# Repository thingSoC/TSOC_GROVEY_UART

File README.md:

# TSOC_GROVEY_UART

The thingSoC GROVEY_UART Base board incorporates a Cypress CY7C65215 Dual Channel USB Bridge, that supports UART, I2C, SPI, and JTAG interfaces in a thingSoC format.

The thingSoC GROVEY_UART Base board has two USB bridge channels, which can be programmed to be either UART, I2C, SPI, JTAG, or Capacitance Sensing (buttons/sliders) Human Input devices.

USB Bridge One (Port 1) and USB Bridge Two (Port 2) are both connected to Grove System compatible connectors, and USB Bridge One (Port 1) is also connected to the thingSoC standard UART channel.

Port1 can be used to program a target microprocessor, at the same time Port2 is used for another purpose (i.e. debug channel, USB to RS-485 bridge, etc).  

It's like having two (2) FTDI adapters in One!

[ 
TSOC_GROVEY_UART](https://github.com/thingSoC/TSOC_GROVEY_UART)

---------------------------------------
## Use it as a Programming Dongle

---------------------------------------
## Use it as a Protocol Adapter

---------------------------------------
## TSOC_GROVEY_UART Model Images

[ 
TSOC_GROVEY_UART](https://github.com/thingSoC/TSOC_GROVEY_UART)

[ 
TSOC_GROVEY_UART](https://github.com/thingSoC/TSOC_GROVEY_UART)

---------------------------------------

## TSOC_GROVEY_UART Status <a name="TSOC_GROVEY_UART_status"/>

Revision 1.0 - 09/02/2016

---------------------------------------

## TSOC_GROVEY_UART Documentation Index <a name="TSOC_GROVEY_UART_documentation_index"/>

[TSOC_GROVEY_UART Project](https://github.com/thingSoC/TSOC_GROVEY_UART/)

[TSOC_GROVEY_UART Hardware](https://github.com/thingSoC/TSOC_GROVEY_UART/tree/master/TSOC_GROVEY_UART/hardware)

---------------------------------------

## thingSoC Documentation Index <a name="thingSoC_documentation_index"/>

[thingSoC Organization Website](http://thingSoC.github.io)

[thingSoC FAQ - Frequently Asked Questions](http://thingsoc.github.io/support/faq.html)

---------------------------------------

[ 
*thingSoC*](http://thingsoc.github.io)

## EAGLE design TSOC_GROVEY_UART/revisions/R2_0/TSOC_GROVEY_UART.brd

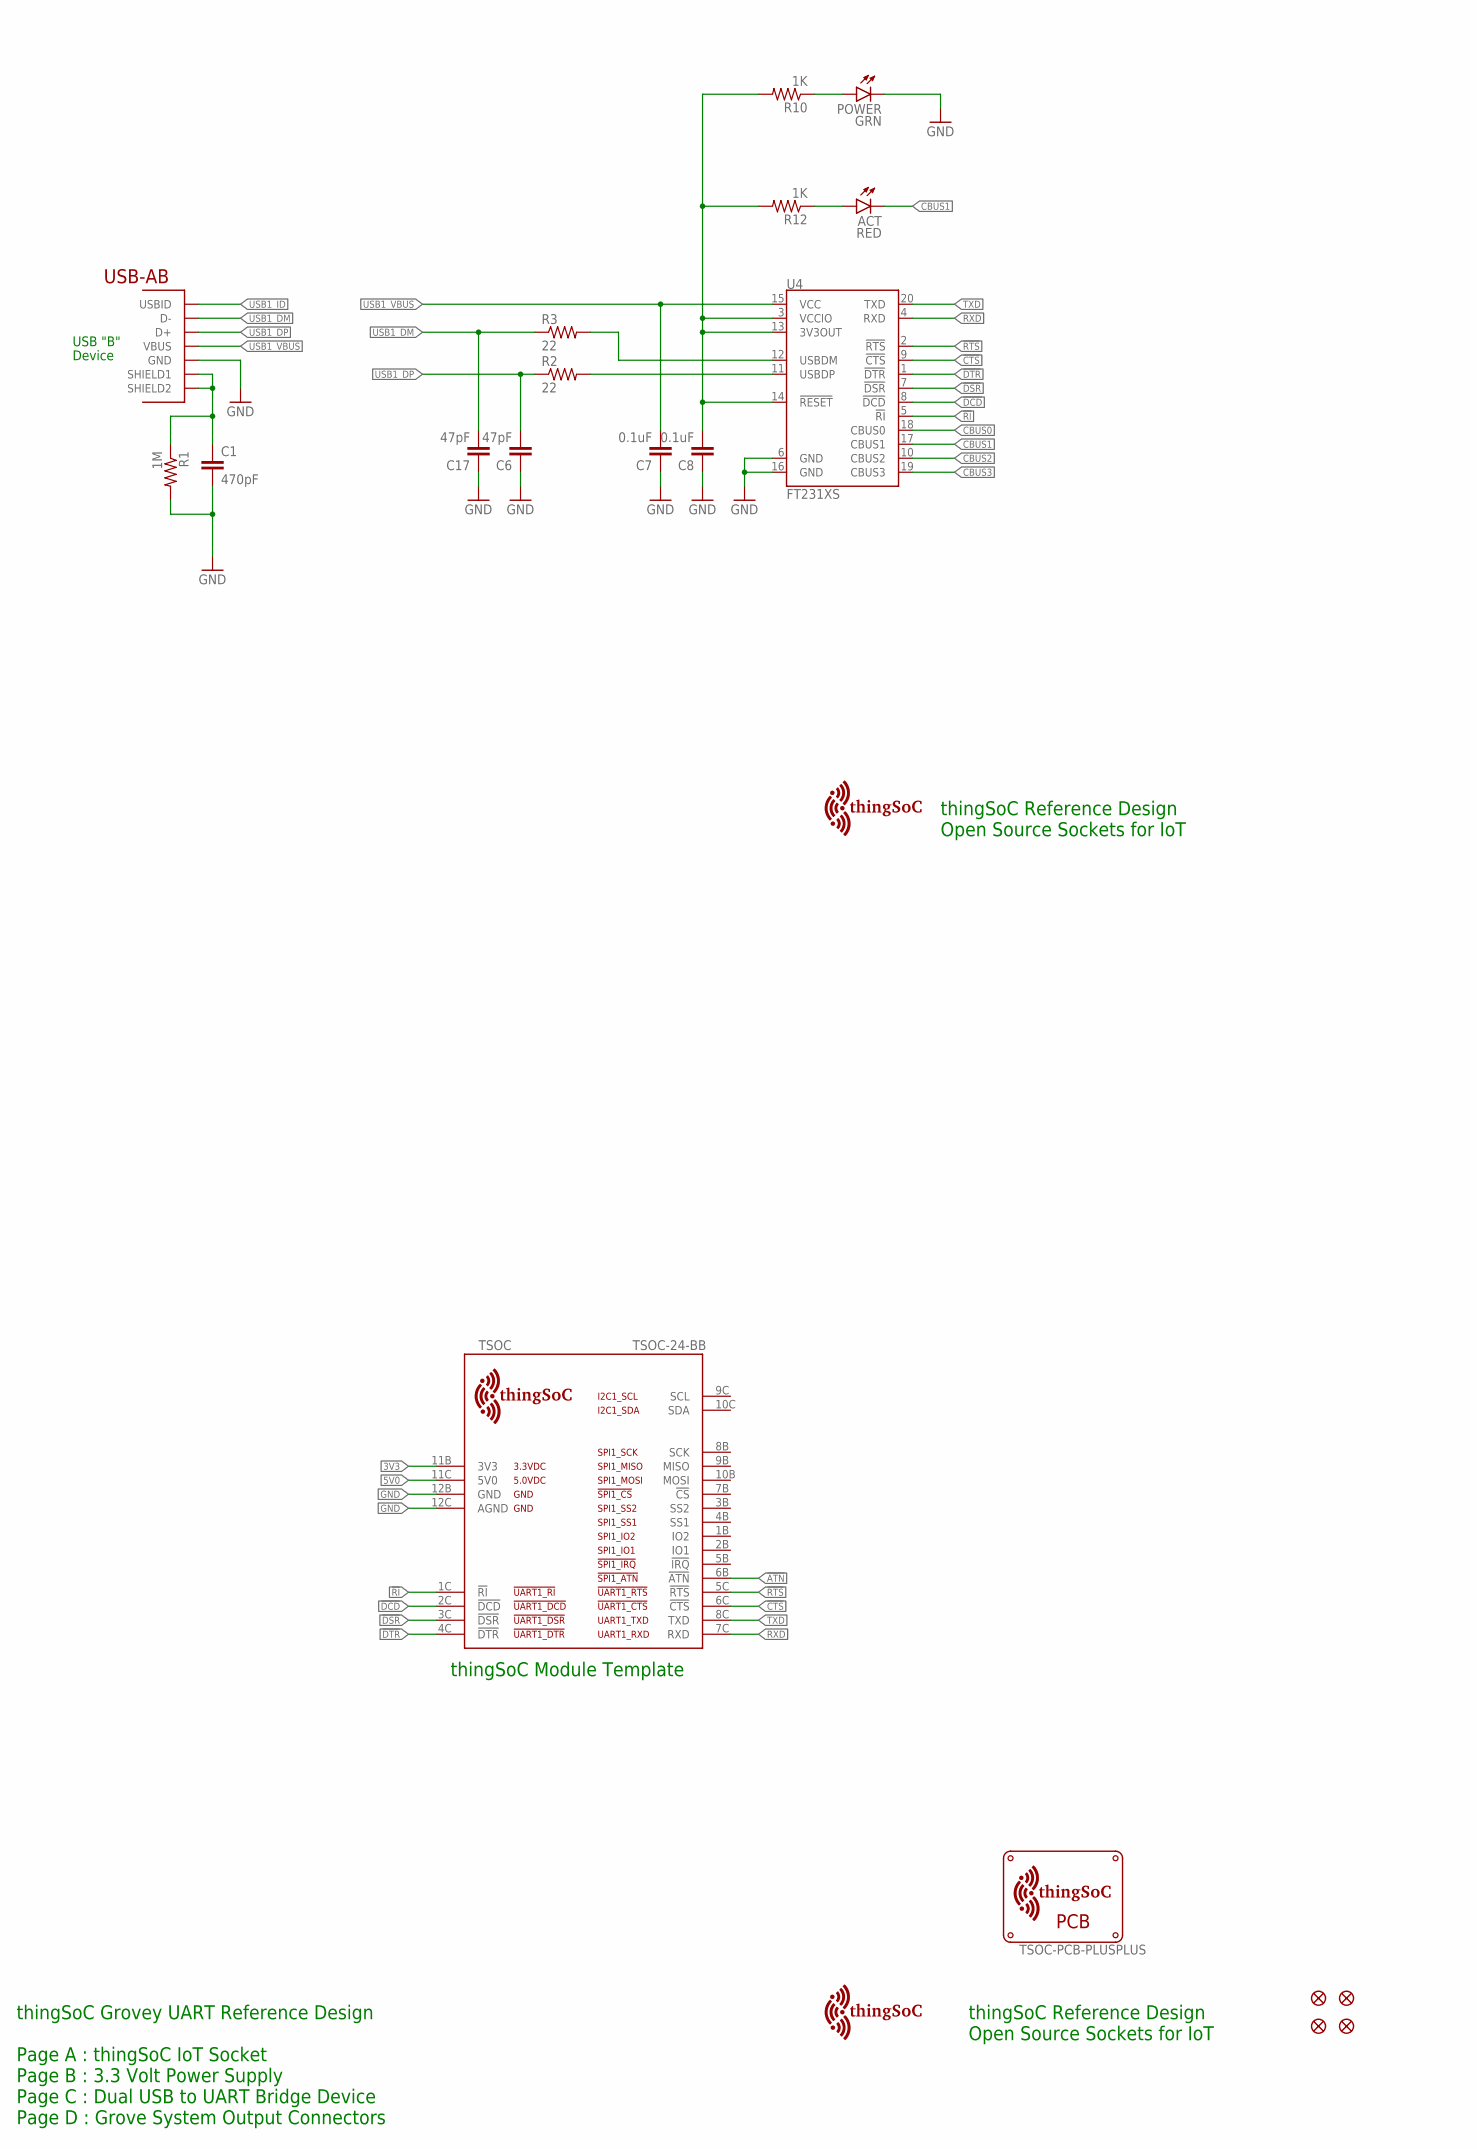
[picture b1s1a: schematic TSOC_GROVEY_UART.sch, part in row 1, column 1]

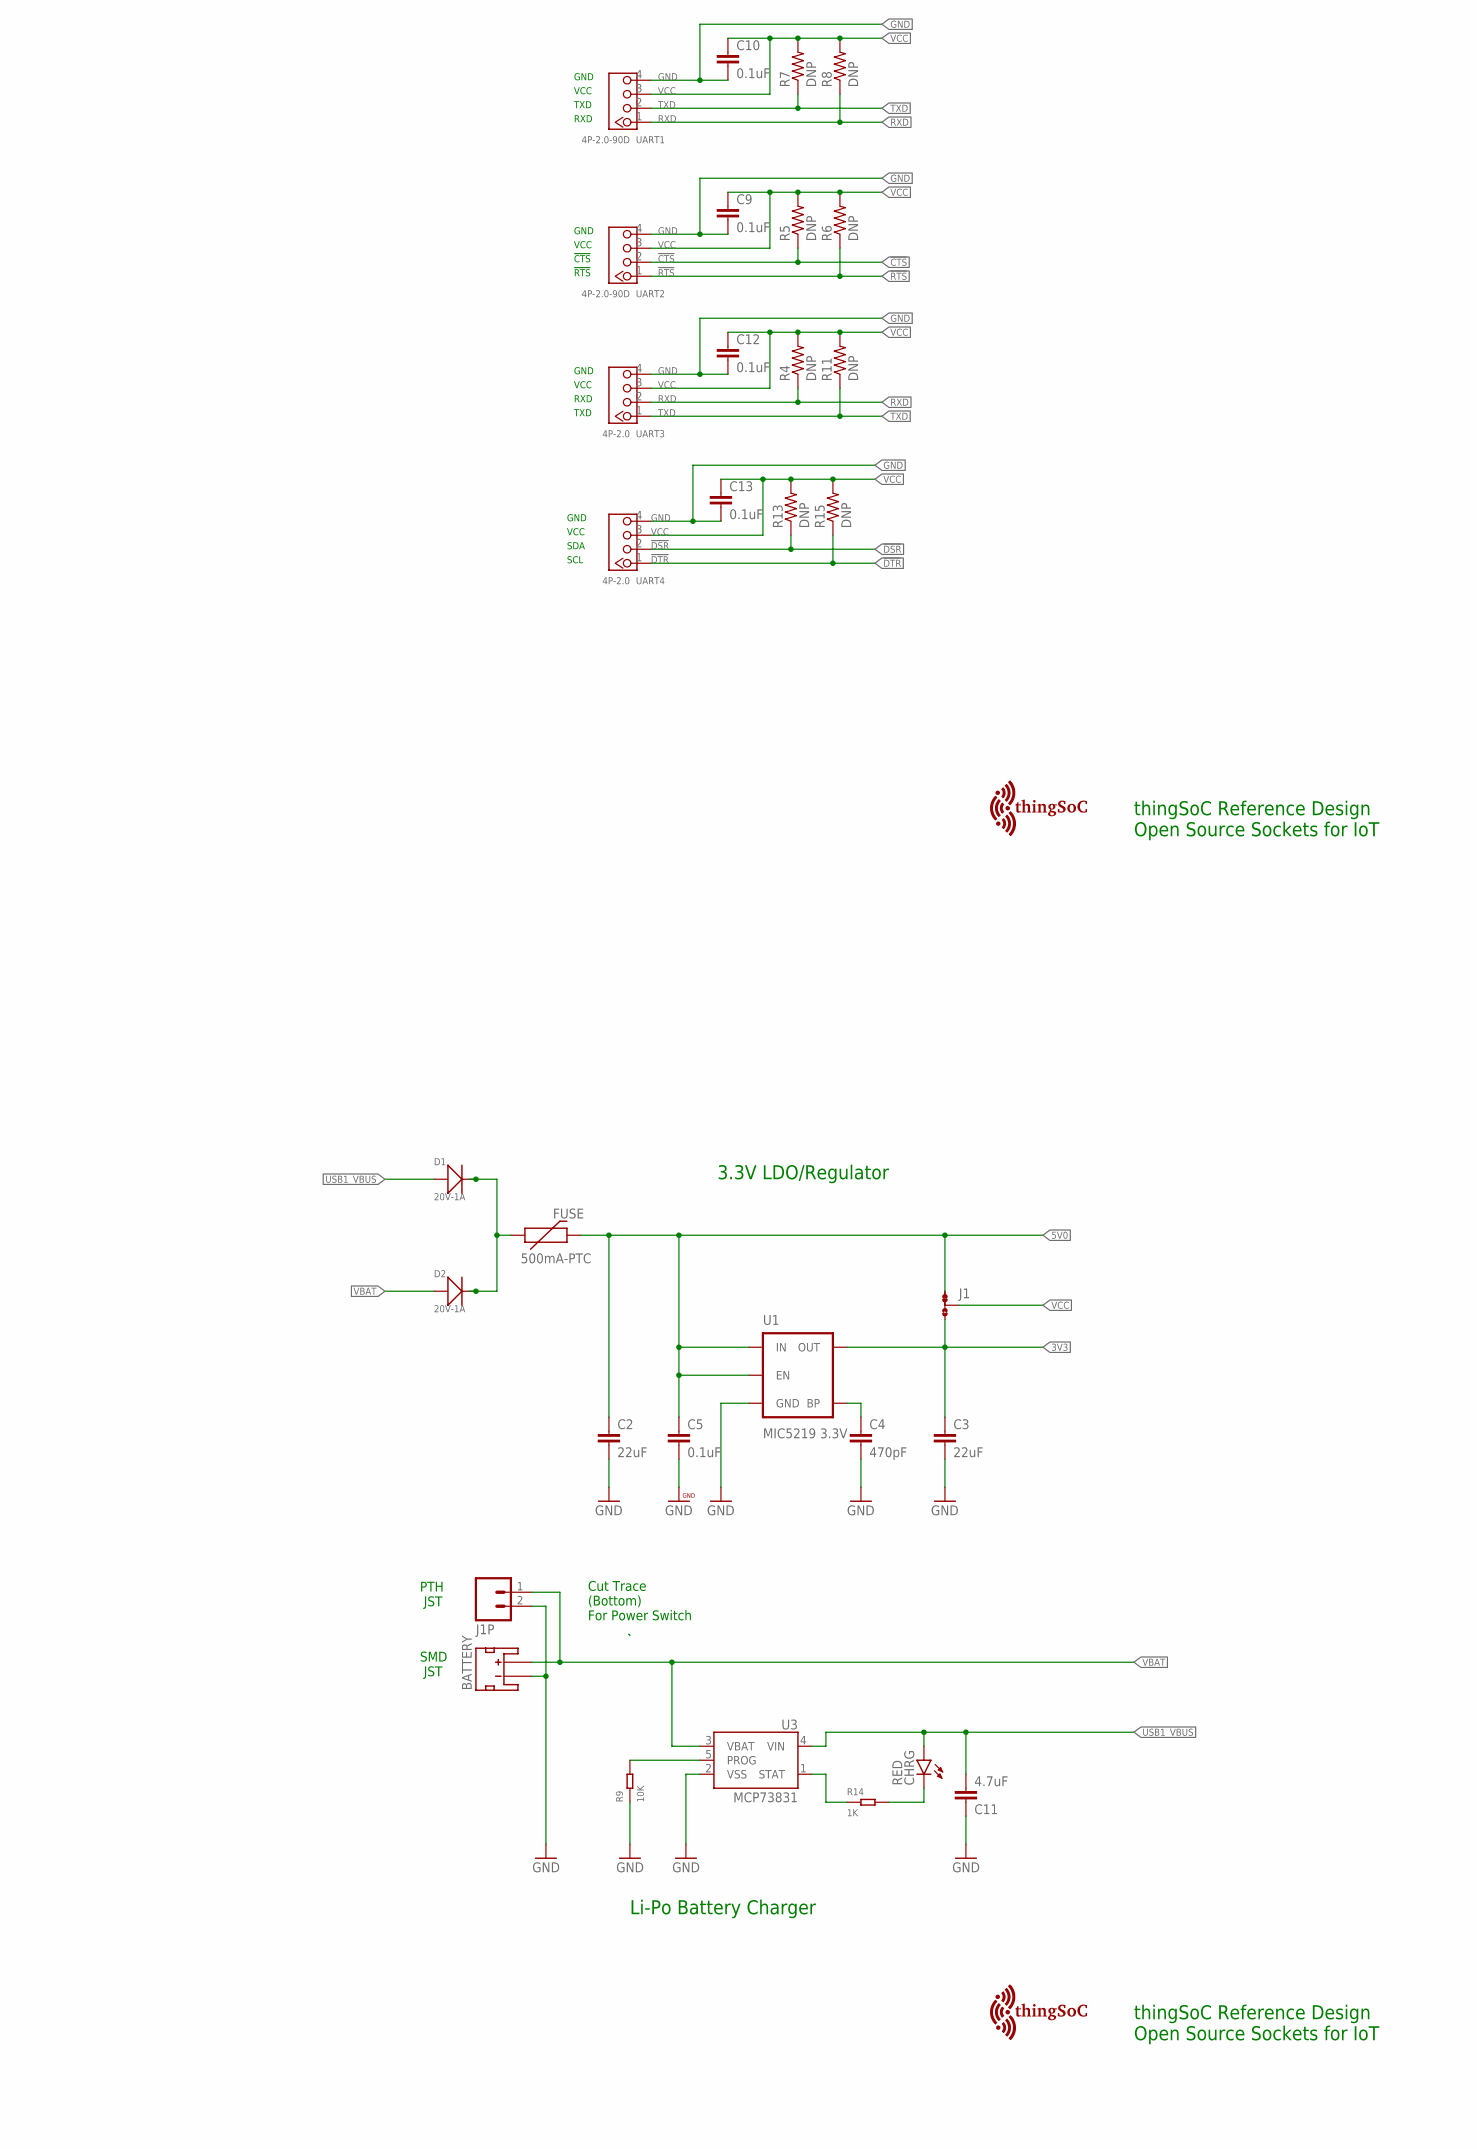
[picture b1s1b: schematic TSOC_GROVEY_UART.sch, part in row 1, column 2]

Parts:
ACT: RED; LED-0603
BATTERY: JST_2MM_MALE; JST-2-SMD
C1, C4: 470pF; EIA-0603
C2, C3: 22uF; EIA-1206
C5, C7, C8: 0.1uF; EIA-0603
C6, C17: 47pF; EIA-0603
C9, C10, C12, C13: 0.1uF; 0603-CAP
C11: 4.7uF; 0402-CAP
CHRG: RED; LED-0603
D1, D2: 20V-1A; SOD-123
FID1, FID2, FID3, FID4: FIDUCIALUFIDUCIAL; MICRO-FIDUCIAL
FUSE: 500mA-PTC; PTC-1206
J1: JMP-3-1_2
J1P: M02-JST-2-PTH-NO_SILK; JST-2-PTH-NS
POWER: GRN; LED-0603
R1: 1M; EIA-0603
R2, R3: 22; EIA-0603
R4, R5, R6, R7, R8, R11, R13, R15: DNP; 0603-RES
R9: 10K; R0603
R10, R12: 1K; EIA-0603
R14: 1K; R0603
TSOC: TSOC-24-BB; TSOC-BB-S24
U1: MIC5219 3.3V; SOT23-5
U3: MCP73831; SOT23-5
U4: FT231XS; SSOP20_L
U$3: TSOC-LOGO-LRG
U$4, U$5, U$6: TSOC-LOGO; TSOC-LOGO-BLANK
U$8: TSOC-PCB-PLUSPLUS; TSOC-BB-BRD-PLUS-PLUS-DIM
UART1, UART2: 4P-2.0-90D; HW4-2.0-90D
UART3, UART4: 4P-2.0; HW4-2.0
USB: USB_AB; USB-AB-MICRO-SMD

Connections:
3V3: C3.1, J1.3, TSOC.11B (3V3), U1.5 (OUT)
3V3U: C8.2, R10.2, R12.2, U4.3 (VCCIO), U4.13 (3V3OUT), U4.14 (!RESET)
5V0: C2.1, C5.1, FUSE.2, J1.1, TSOC.11C (5V0), U1.1 (IN), U1.3 (EN)
!ATN: TSOC.6B (!ATN)
!CTS: R5.1, TSOC.6C (!CTS), U4.9 (!CTS), UART2.2
!DCD: TSOC.2C (!DCD), U4.8 (!DCD)
!DSR: R13.1, TSOC.3C (!DSR), U4.7 (!DSR), UART4.2
!DTR: R15.1, TSOC.4C (!DTR), U4.1 (!DTR), UART4.1
!RI: TSOC.1C (!RI), U4.5 (!RI)
!RTS: R6.1, TSOC.5C (!RTS), U4.2 (!RTS), UART2.1
BYPASS1: C4.1, U1.4 (BP)
CBUS0: U4.18 (CBUS0)
CBUS1: ACT.C, U4.17 (CBUS1)
CBUS2: U4.10 (CBUS2)
CBUS3: U4.19 (CBUS3)
CLED: CHRG.C, R14.2
CSTAT: R14.1, U3.1 (STAT)
GND: BATTERY.1 (-), C1.2, C2.2, C3.2, C4.2, C5.2, C6.1, C7.1, C8.1, C9.2, C10.2, C11.1, C12.2, C13.2, C17.1, J1P.2, POWER.C, R1.2, R9.1, TSOC.12B (GND), TSOC.12C (AGND), U1.2 (GND), U3.2 (VSS), U4.6 (GND), U4.16 (GND), UART1.4, UART2.4, UART3.4, UART4.4, USB.GND
GRN: POWER.A, R10.1
unnamed: D1.-, D2.-, FUSE.1
RXD: R4.1, R8.1, TSOC.7C (RXD), U4.4 (RXD), UART1.1, UART3.2
TXD: R7.1, R11.1, TSOC.8C (TXD), U4.20 (TXD), UART1.2, UART3.1
USB1_DM: C17.2, R3.1, USB.D-
USB1_DP: C6.2, R2.1, USB.D+
USB1_ID: USB.ID (USBID)
USB1_M: R3.2, U4.12 (USBDM)
USB1_P: R2.2, U4.11 (USBDP)
USB1_SHIELD: C1.1, R1.1, USB.SHIELD1, USB.SHIELD2
USB1_VBUS: C7.2, C11.2, CHRG.A, D1.+, U3.4 (VIN), U4.15 (VCC), USB.VBUS
VBAT: BATTERY.2 (+), D2.+, J1P.1, U3.3 (VBAT)
VB_PROG: R9.2, U3.5 (PROG)
VCC: C9.1, C10.1, C12.1, C13.1, J1.2, R4.2, R5.2, R6.2, R7.2, R8.2, R11.2, R13.2, R15.2, UART1.3, UART2.3, UART3.3, UART4.3
YEL: ACT.A, R12.1

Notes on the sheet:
thingSoC Reference Design Open Source Sockets for IoT
USB "B"
Device
thingSoC Grovey UART Reference Design Page A : thingSoC IoT Socket Page B : 3.3 Volt Power Supply Page C : Dual USB to UART Bridge Device Page D : Grove System Output Connectors
thingSoC Module Template
3.3V LDO/Regulator
GND
VCC
RXD
TXD
!CTS
!RTS
Li-Po Battery Charger
Cut Trace (Bottom) For Power Switch
SMD JST
PTH JST
SDA
SCL

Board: 2 copper layers, 58 parts (2 on the bottom side), 28 nets, no tracks yet.

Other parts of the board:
U$1, U$7: TSOC-LOGO-SMALL; TSOC-LOGO-SML

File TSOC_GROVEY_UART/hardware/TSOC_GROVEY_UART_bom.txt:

Partlist exported from /data/customers/PatternAgents/eagle/TSOC_Modules/TSOC_GROVEY_UART/TSOC_GROVEY_UART/TSOC_GROVEY_UART.sch at 8/25/16 1:26 PM

Qty Value              Device                          Package                  Parts                  Description                                                                                                                                                                               
2                      JMP-2-NO                        JMP-2-NO                 SCL, SDA               Two Terminal Jumper - Normally Open                                                                                                                                                       
3   0.1uF              CAP-0603                        EIA-0603                 C5, C7, C8             Ceramic Capacitor SMD                                                                                                                                                                     
2   0.1uF              CAP0603-CAP                     0603-CAP                 C9, C10                Capacitor                                                                                                                                                                                 
1   1.0uF              CAP-0603                        EIA-0603                 C6                     Ceramic Capacitor SMD                                                                                                                                                                     
2   10K                RESISTOR-0603                   EIA-0603                 R15, R17                                                                                                                                                                                                         
4   1K                 RESISTOR-0603                   EIA-0603                 R4, R10, R11, R12                                                                                                                                                                                                
1   1M                 RESISTOR-0603                   EIA-0603                 R1                                                                                                                                                                                                               
2   22                 RESISTOR-0603                   EIA-0603                 R2, R3                                                                                                                                                                                                           
1   22K                RESISTOR-0603                   EIA-0603                 R13                                                                                                                                                                                                              
2   22uF               CAP-1206                        EIA-1206                 C2, C3                 Ceramic Capacitor SMD                                                                                                                                                                     
2   470pF              CAP-0603                        EIA-0603                 C1, C4                 Ceramic Capacitor SMD                                                                                                                                                                     
2   4P-2.0-90D         GROVE-CONNECTOR-DIP-90D(4P-2.0) HW4-2.0-90D              UART1, UART2           320110034                                                                                                                                                                                 
1   500mA-PTC          PTCSMD                          PTC-1206                 FUSE                   Resettable Fuse PTC                                                                                                                                                                       
1   BLUE               LED0603                         LED-0603                 PORT2                  LEDs                                                                                                                                                                                      
1   CY7C65215-32-PROTO CY7C65215-32-PROTO              QFN32-PROTO              U2                     Cypress EZ-USB ® CY7C65215-32QFN DUAL CHANNEL USB TO UART/SPI/IC Bridge                                                                                                                   
4   DNP                RESISTOR0603-RES                0603-RES                 R5, R6, R7, R8         Resistor                                                                                                                                                                                  
4   FIDUCIALUFIDUCIAL  FIDUCIALUFIDUCIAL               MICRO-FIDUCIAL           FID1, FID2, FID3, FID4 Fiducial Alignment Points                                                                                                                                                                 
1   GRN                LED0603                         LED-0603                 POWER                  LEDs                                                                                                                                                                                      
2   JMP-3-1_2          JMP-3-1_2                       JMP-3-1_2                J1, J2                 Three Terminal Jumper - 1 & 2 Connected                                                                                                                                                   
1   MIC5219 3.3V       V_REG_MIC52193.3V               SOT23-5                  U1                     V_REG MIC5219                                                                                                                                                                             
1   RED                LED0603                         LED-0603                 SUSPEND                LEDs                                                                                                                                                                                      
1   SP1001-02JTG       SP1001-02JTG                    SC70-3                   ESD                    Littelfuse SP1001-02JTG TVS Diode Array 8pf 15kV Source: 
1   USB_AB             USB_AB                          USB-AB-MICRO-SMD         USB                    This is a USB AB connector that is compatible with USB OTG.                                                                            
1   YELLOW             LED0603                         LED-0603                 PORT1                  LEDs

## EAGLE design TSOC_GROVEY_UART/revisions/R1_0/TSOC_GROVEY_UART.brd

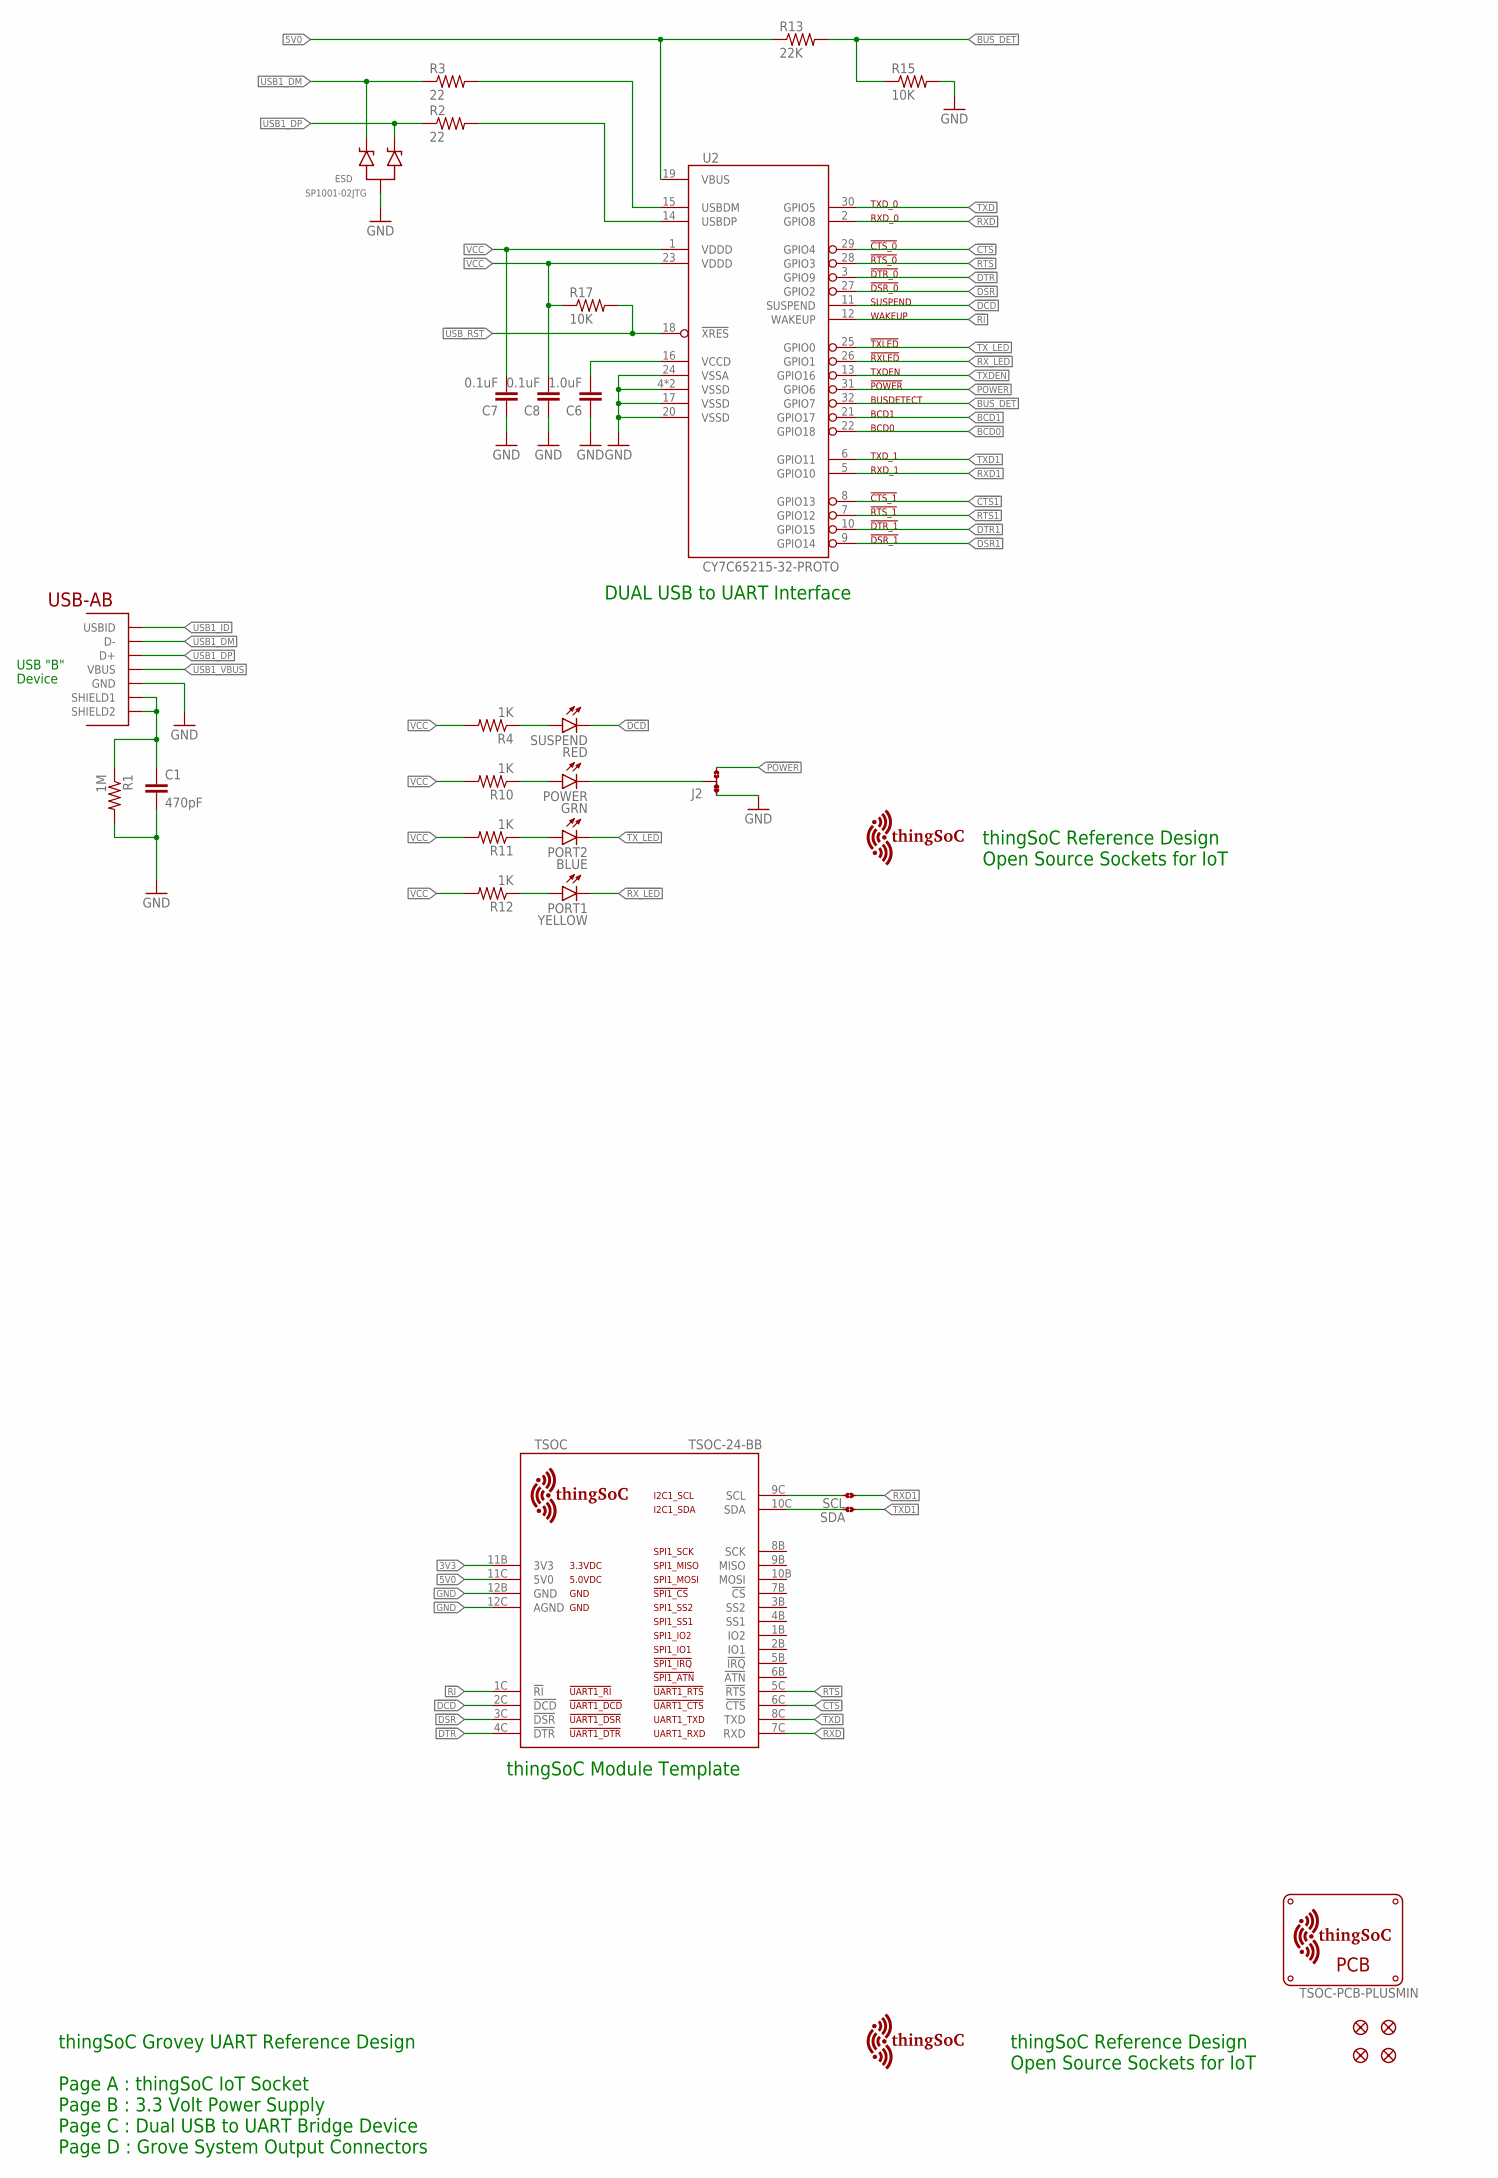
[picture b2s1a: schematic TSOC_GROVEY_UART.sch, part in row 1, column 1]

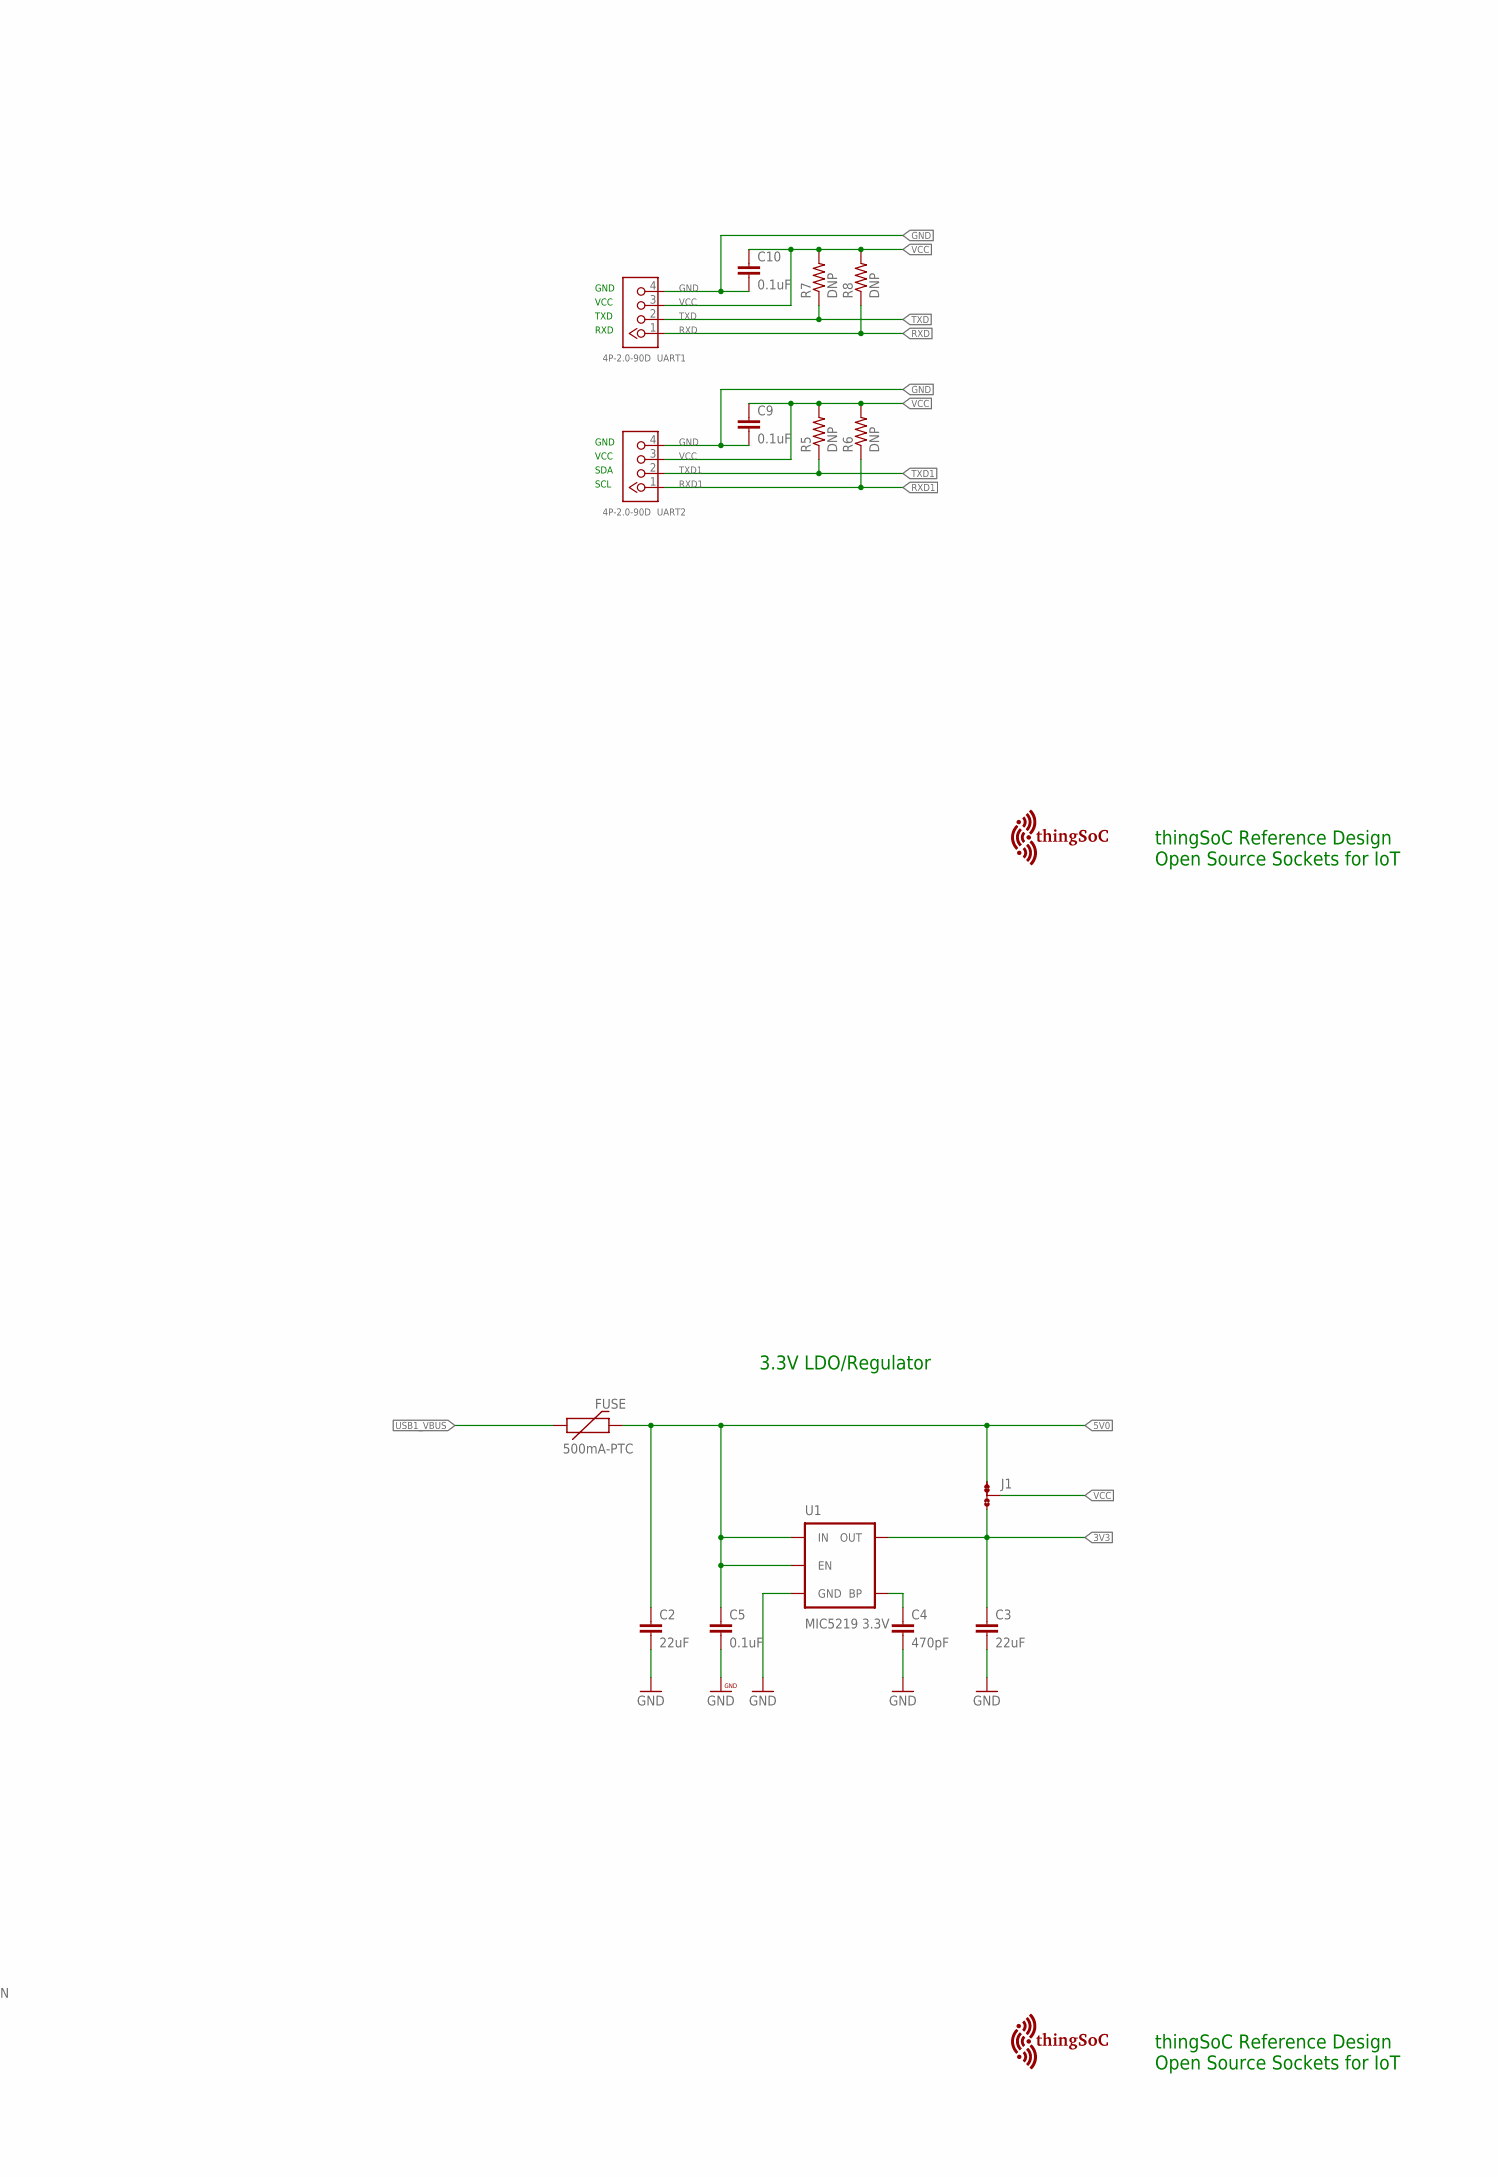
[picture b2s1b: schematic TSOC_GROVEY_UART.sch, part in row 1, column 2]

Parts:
C1, C4: 470pF; EIA-0603
C2, C3: 22uF; EIA-1206
C5, C7, C8: 0.1uF; EIA-0603
C6: 1.0uF; EIA-0603
C9, C10: 0.1uF; 0603-CAP
ESD: SP1001-02JTG; SC70-3
FID1, FID2, FID3, FID4: FIDUCIALUFIDUCIAL; MICRO-FIDUCIAL
FUSE: 500mA-PTC; PTC-1206
J1, J2: JMP-3-1_2
PCB: TSOC-PCB-PLUSMIN; TSOC-BB-BRD-PLUS-MIN-DIM
PORT1: YELLOW; LED-0603
PORT2: BLUE; LED-0603
POWER: GRN; LED-0603
R1: 1M; EIA-0603
R2, R3: 22; EIA-0603
R4, R10, R11, R12: 1K; EIA-0603
R5, R6, R7, R8: DNP; 0603-RES
R13: 22K; EIA-0603
R15, R17: 10K; EIA-0603
SCL: JMP-2-NO
SDA: JMP-2-NO
SUSPEND: RED; LED-0603
TSOC: TSOC-24-BB; TSOC-BB-S24
U1: MIC5219 3.3V; SOT23-5
U2: CY7C65215-32-PROTO; QFN32-PROTO
U$3: TSOC-LOGO-LRG
U$4, U$5, U$6: TSOC-LOGO; TSOC-LOGO-BLANK
UART1, UART2: 4P-2.0-90D; HW4-2.0-90D
USB: USB_AB; USB-AB-MICRO-SMD

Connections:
3V3: C3.1, J1.3, TSOC.11B (3V3), U1.5 (OUT)
5V0: C2.1, C5.1, FUSE.2, J1.1, R13.1, TSOC.11C (5V0), U1.1 (IN), U1.3 (EN), U2.19 (VBUS)
!CTS: TSOC.6C (!CTS), U2.29 (GPIO4)
!CTS1: U2.8 (GPIO13)
!DCD: SUSPEND.C, TSOC.2C (!DCD), U2.11 (SUSPEND)
!DSR: TSOC.3C (!DSR), U2.27 (GPIO2)
!DSR1: U2.9 (GPIO14)
!DTR: TSOC.4C (!DTR), U2.3 (GPIO9)
!DTR1: U2.10 (GPIO15)
!POWER: J2.3, U2.31 (GPIO6)
!RI: TSOC.1C (!RI), U2.12 (WAKEUP)
!RTS: TSOC.5C (!RTS), U2.28 (GPIO3)
!RTS1: U2.7 (GPIO12)
!RX_LED: PORT1.C, U2.26 (GPIO1)
!TX_LED: PORT2.C, U2.25 (GPIO0)
!USB_RST: R17.2, U2.18 (!XRES)
BCD0: U2.22 (GPIO18)
BCD1: U2.21 (GPIO17)
BLU: PORT2.A, R11.1
BUS_DET: R13.2, R15.1, U2.32 (GPIO7)
BYPASS1: C4.1, U1.4 (BP)
GND: C1.2, C2.2, C3.2, C4.2, C5.2, C6.1, C7.1, C8.1, C9.2, C10.2, ESD.3 (A), J2.1, R1.2, R15.2, TSOC.12B (GND), TSOC.12C (AGND), U1.2 (GND), U2.4 (VSSD), U2.17 (VSSD), U2.20 (VSSD), U2.24 (VSSA), U2.EXP (VSSD), UART1.4, UART2.4, USB.GND
GRN: POWER.A, R10.1
PWR: J2.2, POWER.C
RED: R4.1, SUSPEND.A
RXD: R8.1, TSOC.7C (RXD), U2.2 (GPIO8), UART1.1
RXD1: R6.1, SCL.1, U2.5 (GPIO10), UART2.1
SCL: SCL.2, TSOC.9C (SCL)
SDA: SDA.2, TSOC.10C (SDA)
TXD: R7.1, TSOC.8C (TXD), U2.30 (GPIO5), UART1.2
TXD1: R5.1, SDA.1, U2.6 (GPIO11), UART2.2
TXDEN: U2.13 (GPIO16)
USB1_DM: ESD.2 (C2), R3.1, USB.D-
USB1_DP: ESD.1 (C1), R2.1, USB.D+
USB1_ID: USB.ID (USBID)
USB1_M: R3.2, U2.15 (USBDM)
USB1_P: R2.2, U2.14 (USBDP)
USB1_SHIELD: C1.1, R1.1, USB.SHIELD1, USB.SHIELD2
USB1_VBUS: FUSE.1, USB.VBUS
VCC: C7.2, C8.2, C9.1, C10.1, J1.2, R4.2, R5.2, R6.2, R7.2, R8.2, R10.2, R11.2, R12.2, R17.1, U2.1 (VDDD), U2.23 (VDDD), UART1.3, UART2.3
VCCD1: C6.2, U2.16 (VCCD)
YEL: PORT1.A, R12.1

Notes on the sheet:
thingSoC Reference Design Open Source Sockets for IoT
USB "B"
Device
thingSoC Grovey UART Reference Design Page A : thingSoC IoT Socket Page B : 3.3 Volt Power Supply Page C : Dual USB to UART Bridge Device Page D : Grove System Output Connectors
DUAL USB to UART Interface
thingSoC Module Template
3.3V LDO/Regulator
GND
VCC
RXD
TXD
SDA
SCL

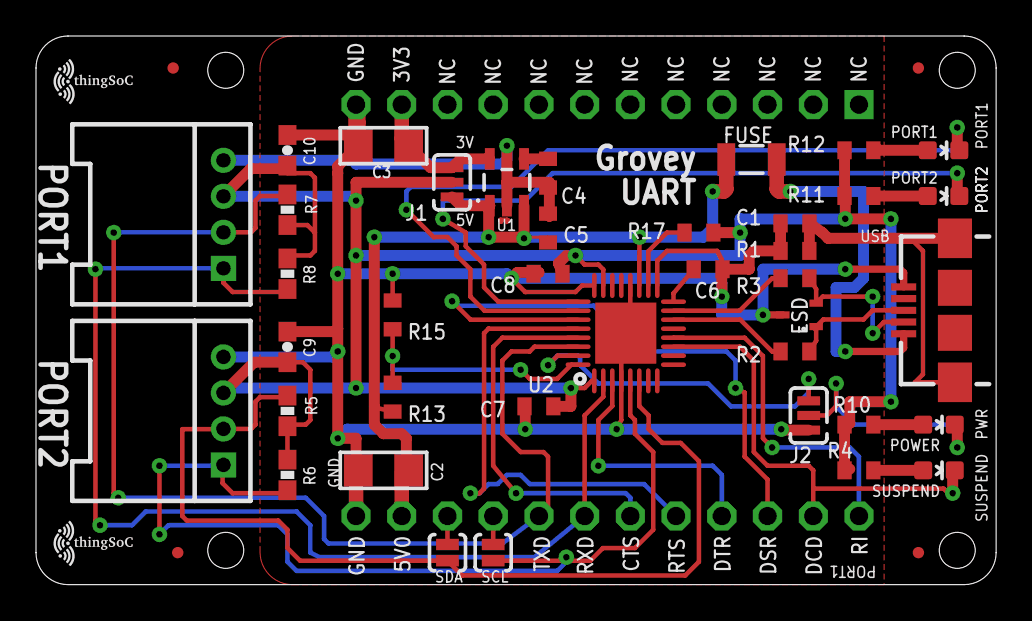
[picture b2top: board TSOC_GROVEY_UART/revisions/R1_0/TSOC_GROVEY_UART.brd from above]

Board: 2 copper layers, 53.3 x 30.5 mm, 51 parts (1 on the bottom side), 34 nets.

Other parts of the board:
U$1, U$7: TSOC-LOGO-SMALL; TSOC-LOGO-SML

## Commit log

2016-09-03 initial version
2016-09-13 add product images

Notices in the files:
parts and their libraries:
thingSoC: License : http://creativecommons.org/licenses/by-sa/4.0
(Creative Commons 4.0)
PatternAgents-Cypress: License : http://creativecommons.org/licenses/by-sa/3.0
(Creative Commons 3.0)
